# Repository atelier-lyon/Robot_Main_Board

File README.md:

# Robot Main Board
## By Florian "FloRide" Reimat

## About
This is the main board

## Images:
### [Schematic](Export/schematics.pdf):

### [PCB](Export/schematics.pdf):
| Front | Bottom |
:------:|:-------:
|| |
### 3D:
| Front | Bottom |
:------:|:-------:
|| |

## Others:
- [Interactive BOM](Export/ibom/Robot-ibom.html) (Download it and use it)

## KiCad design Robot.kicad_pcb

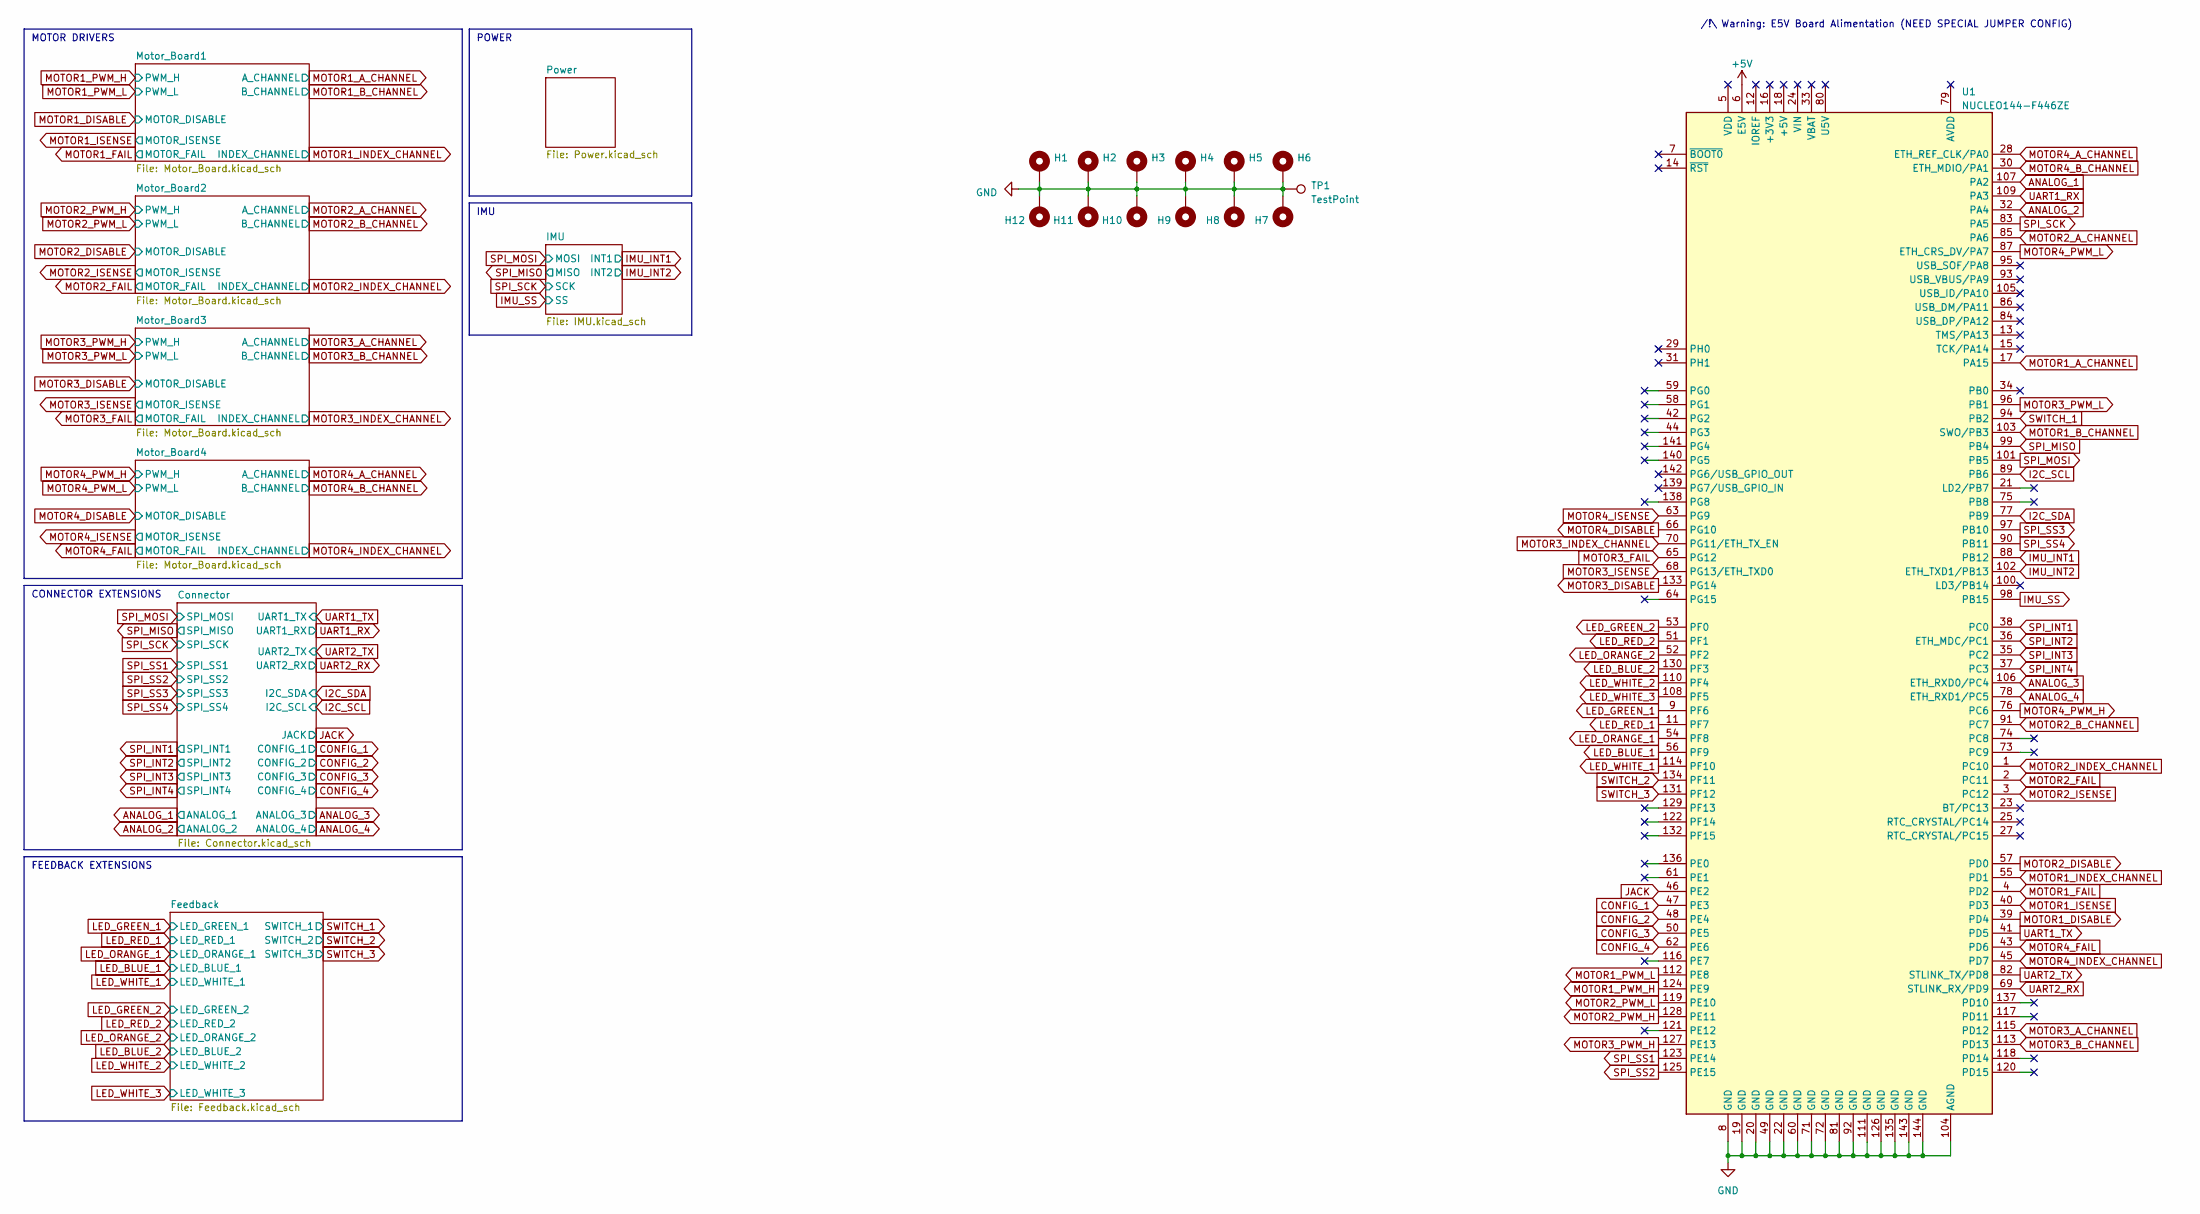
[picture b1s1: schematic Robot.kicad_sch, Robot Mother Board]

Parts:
H1, H2, H3, H4: MountingHole_Pad; MountingHole_4.3mm_M4_Pad
H5, H6, H7, H8, H9, H10, H11, H12: MountingHole_Pad; MountingHole_2.2mm_M2_Pad
TP1: TestPoint; Pin_Croco
U1: NUCLEO144-F446ZE; ST_Morpho_Connector_144_STLink

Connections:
+5V: U1.6 (E5V); also elsewhere on the board
ANALOG_1: U1.107 (PA2); also elsewhere on the board
ANALOG_2: U1.32 (PA4); also elsewhere on the board
ANALOG_3: U1.106 (ETH_RXD0/PC4); also elsewhere on the board
ANALOG_4: U1.78 (ETH_RXD1/PC5); also elsewhere on the board
CONFIG_1: U1.47 (PE3); also elsewhere on the board
CONFIG_2: U1.48 (PE4); also elsewhere on the board
CONFIG_3: U1.50 (PE5); also elsewhere on the board
CONFIG_4: U1.62 (PE6); also elsewhere on the board
GND: H1.1, H2.1, H3.1, H4.1, H5.1, H6.1, H7.1, H8.1, H9.1, H10.1, H11.1, H12.1, TP1.1, U1.8 (GND), U1.19 (GND), U1.20 (GND), U1.22 (GND), U1.49 (GND), U1.60 (GND), U1.71 (GND), U1.72 (GND), U1.81 (GND), U1.92 (GND), U1.104 (AGND), U1.111 (GND), U1.126 (GND), U1.135 (GND), U1.143 (GND), U1.144 (GND); also elsewhere on the board
I2C_SCL: U1.89 (PB6); also elsewhere on the board
I2C_SDA: U1.77 (PB9); also elsewhere on the board
IMU_INT1: U1.88 (PB12); also elsewhere on the board
IMU_INT2: U1.102 (ETH_TXD1/PB13); also elsewhere on the board
IMU_SS: U1.98 (PB15); also elsewhere on the board
JACK: U1.46 (PE2); also elsewhere on the board
LED_BLUE_1: U1.56 (PF9); also elsewhere on the board
LED_BLUE_2: U1.130 (PF3); also elsewhere on the board
LED_GREEN_1: U1.9 (PF6); also elsewhere on the board
LED_GREEN_2: U1.53 (PF0); also elsewhere on the board
LED_ORANGE_1: U1.54 (PF8); also elsewhere on the board
LED_ORANGE_2: U1.52 (PF2); also elsewhere on the board
LED_RED_1: U1.11 (PF7); also elsewhere on the board
LED_RED_2: U1.51 (PF1); also elsewhere on the board
LED_WHITE_1: U1.114 (PF10); also elsewhere on the board
LED_WHITE_2: U1.110 (PF4); also elsewhere on the board
LED_WHITE_3: U1.108 (PF5); also elsewhere on the board
MOTOR1_A_CHANNEL: U1.17 (PA15); also elsewhere on the board
MOTOR1_B_CHANNEL: U1.103 (SWO/PB3); also elsewhere on the board
MOTOR1_DISABLE: U1.39 (PD4); also elsewhere on the board
MOTOR1_FAIL: U1.4 (PD2); also elsewhere on the board
MOTOR1_INDEX_CHANNEL: U1.55 (PD1); also elsewhere on the board
MOTOR1_ISENSE: U1.40 (PD3); also elsewhere on the board
MOTOR1_PWM_H: U1.124 (PE9); also elsewhere on the board
MOTOR1_PWM_L: U1.112 (PE8); also elsewhere on the board
MOTOR2_A_CHANNEL: U1.85 (PA6); also elsewhere on the board
MOTOR2_B_CHANNEL: U1.91 (PC7); also elsewhere on the board
MOTOR2_DISABLE: U1.57 (PD0); also elsewhere on the board
MOTOR2_FAIL: U1.2 (PC11); also elsewhere on the board
MOTOR2_INDEX_CHANNEL: U1.1 (PC10); also elsewhere on the board
MOTOR2_ISENSE: U1.3 (PC12); also elsewhere on the board
MOTOR2_PWM_H: U1.128 (PE11); also elsewhere on the board
MOTOR2_PWM_L: U1.119 (PE10); also elsewhere on the board
MOTOR3_A_CHANNEL: U1.115 (PD12); also elsewhere on the board
MOTOR3_B_CHANNEL: U1.113 (PD13); also elsewhere on the board
MOTOR3_DISABLE: U1.133 (PG14); also elsewhere on the board
MOTOR3_FAIL: U1.65 (PG12); also elsewhere on the board
MOTOR3_INDEX_CHANNEL: U1.70 (PG11/ETH_TX_EN); also elsewhere on the board
MOTOR3_ISENSE: U1.68 (PG13/ETH_TXD0); also elsewhere on the board
MOTOR3_PWM_H: U1.127 (PE13); also elsewhere on the board
MOTOR3_PWM_L: U1.96 (PB1); also elsewhere on the board
MOTOR4_A_CHANNEL: U1.28 (ETH_REF_CLK/PA0); also elsewhere on the board
MOTOR4_B_CHANNEL: U1.30 (ETH_MDIO/PA1); also elsewhere on the board
MOTOR4_DISABLE: U1.66 (PG10); also elsewhere on the board
MOTOR4_FAIL: U1.43 (PD6); also elsewhere on the board
MOTOR4_INDEX_CHANNEL: U1.45 (PD7); also elsewhere on the board
MOTOR4_ISENSE: U1.63 (PG9); also elsewhere on the board
MOTOR4_PWM_H: U1.76 (PC6); also elsewhere on the board
MOTOR4_PWM_L: U1.87 (ETH_CRS_DV/PA7); also elsewhere on the board
SPI_INT1: U1.38 (PC0); also elsewhere on the board
SPI_INT2: U1.36 (ETH_MDC/PC1); also elsewhere on the board
SPI_INT3: U1.35 (PC2); also elsewhere on the board
SPI_INT4: U1.37 (PC3); also elsewhere on the board
SPI_MISO: U1.99 (PB4); also elsewhere on the board
SPI_MOSI: U1.101 (PB5); also elsewhere on the board
SPI_SCK: U1.83 (PA5); also elsewhere on the board
SPI_SS1: U1.123 (PE14); also elsewhere on the board
SPI_SS2: U1.125 (PE15); also elsewhere on the board
SPI_SS3: U1.97 (PB10); also elsewhere on the board
SPI_SS4: U1.90 (PB11); also elsewhere on the board
SWITCH_1: U1.94 (PB2); also elsewhere on the board
SWITCH_2: U1.134 (PF11); also elsewhere on the board
SWITCH_3: U1.131 (PF12); also elsewhere on the board
UART1_RX: U1.109 (PA3); also elsewhere on the board
UART1_TX: U1.41 (PD5); also elsewhere on the board
UART2_RX: U1.69 (STLINK_RX/PD9); also elsewhere on the board
UART2_TX: U1.82 (STLINK_TX/PD8); also elsewhere on the board

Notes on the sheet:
IMU
POWER
CONNECTOR EXTENSIONS
/!\ Warning: E5V Board Alimentation (NEED SPECIAL JUMPER CONFIG)
FEEDBACK EXTENSIONS
MOTOR DRIVERS

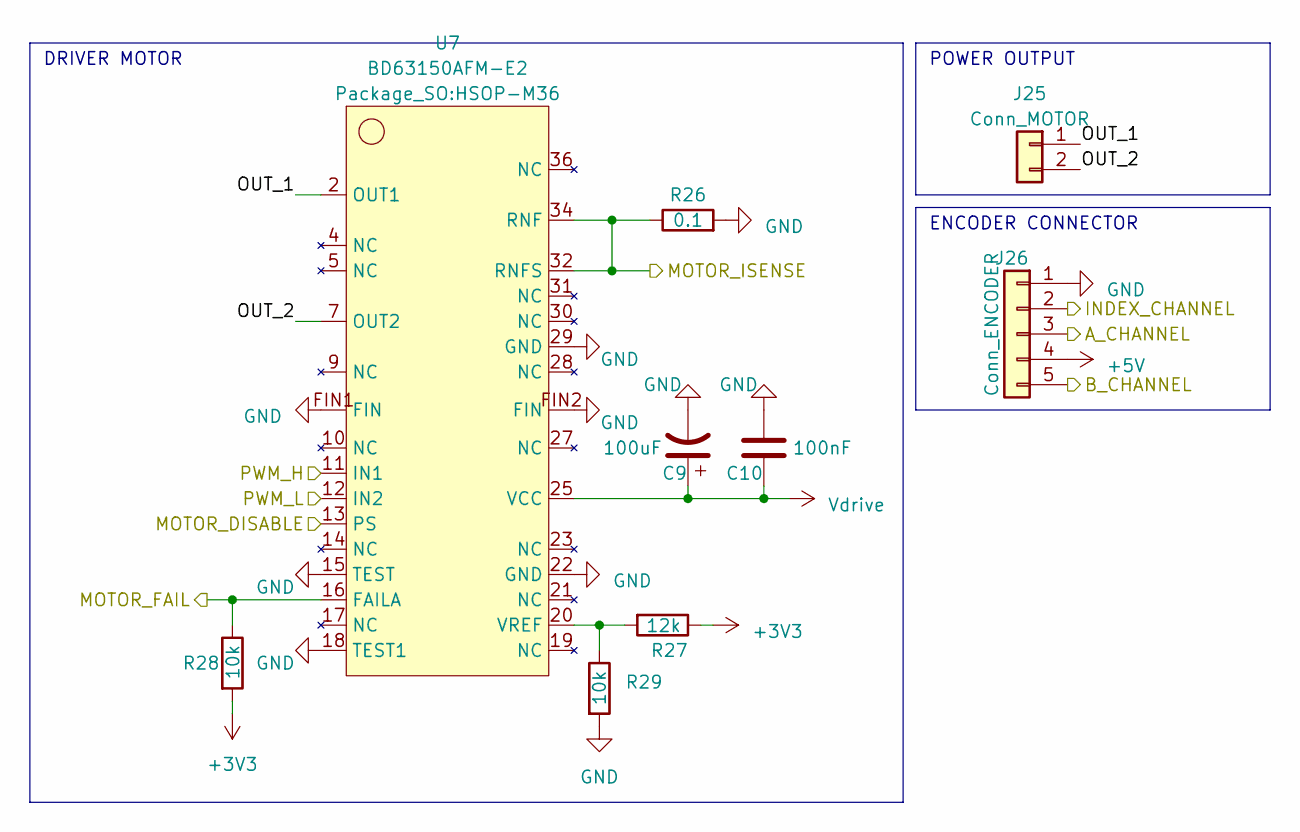
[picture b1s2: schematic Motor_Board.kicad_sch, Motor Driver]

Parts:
C9: 100uF; CP_Radial_D8.0mm_P3.50mm
C10: 100nF; C_0805_2012Metric_Pad1.18x1.45mm_HandSolder
J25: Conn_MOTOR; JST_VH_B2P-VH-B_1x02_P3.96mm_Vertical
J26: Conn_ENCODER; JST_XH_B5B-XH-A_1x05_P2.50mm_Vertical
R26: 0.1; R_2512_6332Metric_Pad1.40x3.35mm_HandSolder
R27: 12k; R_0805_2012Metric_Pad1.20x1.40mm_HandSolder
R28, R29: 10k; R_0805_2012Metric_Pad1.20x1.40mm_HandSolder
U7: BD63150AFM-E2; HSOP-M36

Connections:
+3V3: R27.1, R28.2; also elsewhere on the board
+5V: J26.4; also elsewhere on the board
/Motor_Board1/OUT_1: J25.1, U7.2 (OUT1)
/Motor_Board1/OUT_2: J25.2, U7.7 (OUT2)
GND: C9.2, C10.2, J26.1, R26.2, R29.2, U7.15 (TEST), U7.18 (TEST1), U7.22 (GND), U7.29 (GND), U7.FIN1 (FIN), U7.FIN2 (FIN); also elsewhere on the board
MOTOR1_A_CHANNEL: J26.3; also elsewhere on the board
MOTOR1_B_CHANNEL: J26.5; also elsewhere on the board
MOTOR1_DISABLE: U7.13 (PS); also elsewhere on the board
MOTOR1_FAIL: R28.1, U7.16 (FAILA); also elsewhere on the board
MOTOR1_INDEX_CHANNEL: J26.2; also elsewhere on the board
MOTOR1_ISENSE: R26.1, U7.32 (RNFS), U7.34 (RNF); also elsewhere on the board
MOTOR1_PWM_H: U7.11 (IN1); also elsewhere on the board
MOTOR1_PWM_L: U7.12 (IN2); also elsewhere on the board
unnamed: R27.2, R29.1, U7.20 (VREF)
Vdrive: C9.1, C10.1, U7.25 (VCC); also elsewhere on the board

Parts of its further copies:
C11, C13, C15: 100uF; CP_Radial_D8.0mm_P3.50mm
C12, C14, C16: 100nF; C_0805_2012Metric_Pad1.18x1.45mm_HandSolder
J27, J29, J31: Conn_MOTOR; JST_VH_B2P-VH-B_1x02_P3.96mm_Vertical
J28, J30, J32: Conn_ENCODER; JST_XH_B5B-XH-A_1x05_P2.50mm_Vertical
R30, R34, R38: 0.1; R_2512_6332Metric_Pad1.40x3.35mm_HandSolder
R31, R35, R39: 12k; R_0805_2012Metric_Pad1.20x1.40mm_HandSolder
R32, R33, R36, R37, R40, R41: 10k; R_0805_2012Metric_Pad1.20x1.40mm_HandSolder
U8, U9, U10: BD63150AFM-E2; HSOP-M36

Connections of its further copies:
+3V3: R31.1, R32.2, R35.1, R36.2, R39.1, R40.2; also elsewhere on the board
+5V: J28.4, J30.4, J32.4; also elsewhere on the board
/Motor_Board2/OUT_1: J27.1, U8.2 (OUT1)
/Motor_Board2/OUT_2: J27.2, U8.7 (OUT2)
/Motor_Board3/OUT_1: J29.1, U9.2 (OUT1)
/Motor_Board3/OUT_2: J29.2, U9.7 (OUT2)
/Motor_Board4/OUT_1: J31.1, U10.2 (OUT1)
/Motor_Board4/OUT_2: J31.2, U10.7 (OUT2)
GND: C11.2, C12.2, C13.2, C14.2, C15.2, C16.2, J28.1, J30.1, J32.1, R30.2, R33.2, R34.2, R37.2, R38.2, R41.2, U8.15 (TEST), U8.18 (TEST1), U8.22 (GND), U8.29 (GND), U8.FIN1 (FIN), U8.FIN2 (FIN), U9.15 (TEST), U9.18 (TEST1), U9.22 (GND), U9.29 (GND), U9.FIN1 (FIN), U9.FIN2 (FIN), U10.15 (TEST), U10.18 (TEST1), U10.22 (GND), U10.29 (GND), U10.FIN1 (FIN), U10.FIN2 (FIN); also elsewhere on the board
MOTOR2_A_CHANNEL: J28.3; also elsewhere on the board
MOTOR2_B_CHANNEL: J28.5; also elsewhere on the board
MOTOR2_DISABLE: U8.13 (PS); also elsewhere on the board
MOTOR2_FAIL: R32.1, U8.16 (FAILA); also elsewhere on the board
MOTOR2_INDEX_CHANNEL: J28.2; also elsewhere on the board
MOTOR2_ISENSE: R30.1, U8.32 (RNFS), U8.34 (RNF); also elsewhere on the board
MOTOR2_PWM_H: U8.11 (IN1); also elsewhere on the board
MOTOR2_PWM_L: U8.12 (IN2); also elsewhere on the board
MOTOR3_A_CHANNEL: J30.3; also elsewhere on the board
MOTOR3_B_CHANNEL: J30.5; also elsewhere on the board
MOTOR3_DISABLE: U9.13 (PS); also elsewhere on the board
MOTOR3_FAIL: R36.1, U9.16 (FAILA); also elsewhere on the board
MOTOR3_INDEX_CHANNEL: J30.2; also elsewhere on the board
MOTOR3_ISENSE: R34.1, U9.32 (RNFS), U9.34 (RNF); also elsewhere on the board
MOTOR3_PWM_H: U9.11 (IN1); also elsewhere on the board
MOTOR3_PWM_L: U9.12 (IN2); also elsewhere on the board
MOTOR4_A_CHANNEL: J32.3; also elsewhere on the board
MOTOR4_B_CHANNEL: J32.5; also elsewhere on the board
MOTOR4_DISABLE: U10.13 (PS); also elsewhere on the board
MOTOR4_FAIL: R40.1, U10.16 (FAILA); also elsewhere on the board
MOTOR4_INDEX_CHANNEL: J32.2; also elsewhere on the board
MOTOR4_ISENSE: R38.1, U10.32 (RNFS), U10.34 (RNF); also elsewhere on the board
MOTOR4_PWM_H: U10.11 (IN1); also elsewhere on the board
MOTOR4_PWM_L: U10.12 (IN2); also elsewhere on the board
unnamed: R31.2, R33.1, U8.20 (VREF)
unnamed: R35.2, R37.1, U9.20 (VREF)
unnamed: R39.2, R41.1, U10.20 (VREF)
Vdrive: C11.1, C12.1, C13.1, C14.1, C15.1, C16.1, U8.25 (VCC), U9.25 (VCC), U10.25 (VCC); also elsewhere on the board

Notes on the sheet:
ENCODER CONNECTOR
POWER OUTPUT
DRIVER MOTOR

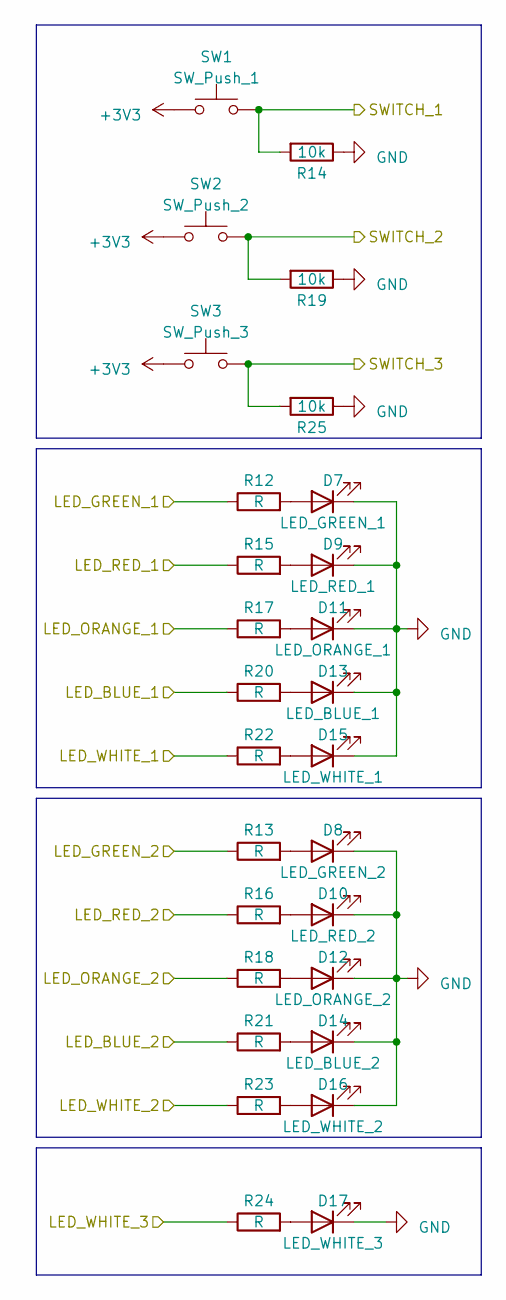
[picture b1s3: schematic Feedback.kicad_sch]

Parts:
D7: LED_GREEN_1; LED_0805_2012Metric_Pad1.15x1.40mm_HandSolder
D8: LED_GREEN_2; LED_0805_2012Metric_Pad1.15x1.40mm_HandSolder
D9: LED_RED_1; LED_0805_2012Metric_Pad1.15x1.40mm_HandSolder
D10: LED_RED_2; LED_0805_2012Metric_Pad1.15x1.40mm_HandSolder
D11: LED_ORANGE_1; LED_0805_2012Metric_Pad1.15x1.40mm_HandSolder
D12: LED_ORANGE_2; LED_0805_2012Metric_Pad1.15x1.40mm_HandSolder
D13: LED_BLUE_1; LED_0805_2012Metric_Pad1.15x1.40mm_HandSolder
D14: LED_BLUE_2; LED_0805_2012Metric_Pad1.15x1.40mm_HandSolder
D15: LED_WHITE_1; LED_0805_2012Metric_Pad1.15x1.40mm_HandSolder
D16: LED_WHITE_2; LED_0805_2012Metric_Pad1.15x1.40mm_HandSolder
D17: LED_WHITE_3; LED_0805_2012Metric_Pad1.15x1.40mm_HandSolder
R12, R13, R15, R16, R17, R18, R20, R21, R22, R23, R24: R; R_0805_2012Metric_Pad1.20x1.40mm_HandSolder
R14, R19, R25: 10k; R_0805_2012Metric_Pad1.20x1.40mm_HandSolder
SW1: SW_Push_1; SW_Tactile_Straight_KSL0Axx1LFTR
SW2: SW_Push_2; SW_Tactile_Straight_KSL0Axx1LFTR
SW3: SW_Push_3; SW_Tactile_Straight_KSL0Axx1LFTR

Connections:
+3V3: SW1.1, SW2.1, SW3.1; also elsewhere on the board
GND: D7.1 (K), D8.1 (K), D9.1 (K), D10.1 (K), D11.1 (K), D12.1 (K), D13.1 (K), D14.1 (K), D15.1 (K), D16.1 (K), D17.1 (K), R14.1, R19.1, R25.1; also elsewhere on the board
LED_BLUE_1: R20.1; also elsewhere on the board
LED_BLUE_2: R21.1; also elsewhere on the board
LED_GREEN_1: R12.1; also elsewhere on the board
LED_GREEN_2: R13.1; also elsewhere on the board
LED_ORANGE_1: R17.1; also elsewhere on the board
LED_ORANGE_2: R18.1; also elsewhere on the board
LED_RED_1: R15.1; also elsewhere on the board
LED_RED_2: R16.1; also elsewhere on the board
LED_WHITE_1: R22.1; also elsewhere on the board
LED_WHITE_2: R23.1; also elsewhere on the board
LED_WHITE_3: R24.1; also elsewhere on the board
unnamed: D7.2 (A), R12.2
unnamed: D8.2 (A), R13.2
unnamed: D9.2 (A), R15.2
unnamed: D10.2 (A), R16.2
unnamed: D11.2 (A), R17.2
unnamed: D12.2 (A), R18.2
unnamed: D13.2 (A), R20.2
unnamed: D14.2 (A), R21.2
unnamed: D15.2 (A), R22.2
unnamed: D16.2 (A), R23.2
unnamed: D17.2 (A), R24.2
SWITCH_1: R14.2, SW1.2; also elsewhere on the board
SWITCH_2: R19.2, SW2.2; also elsewhere on the board
SWITCH_3: R25.2, SW3.2; also elsewhere on the board

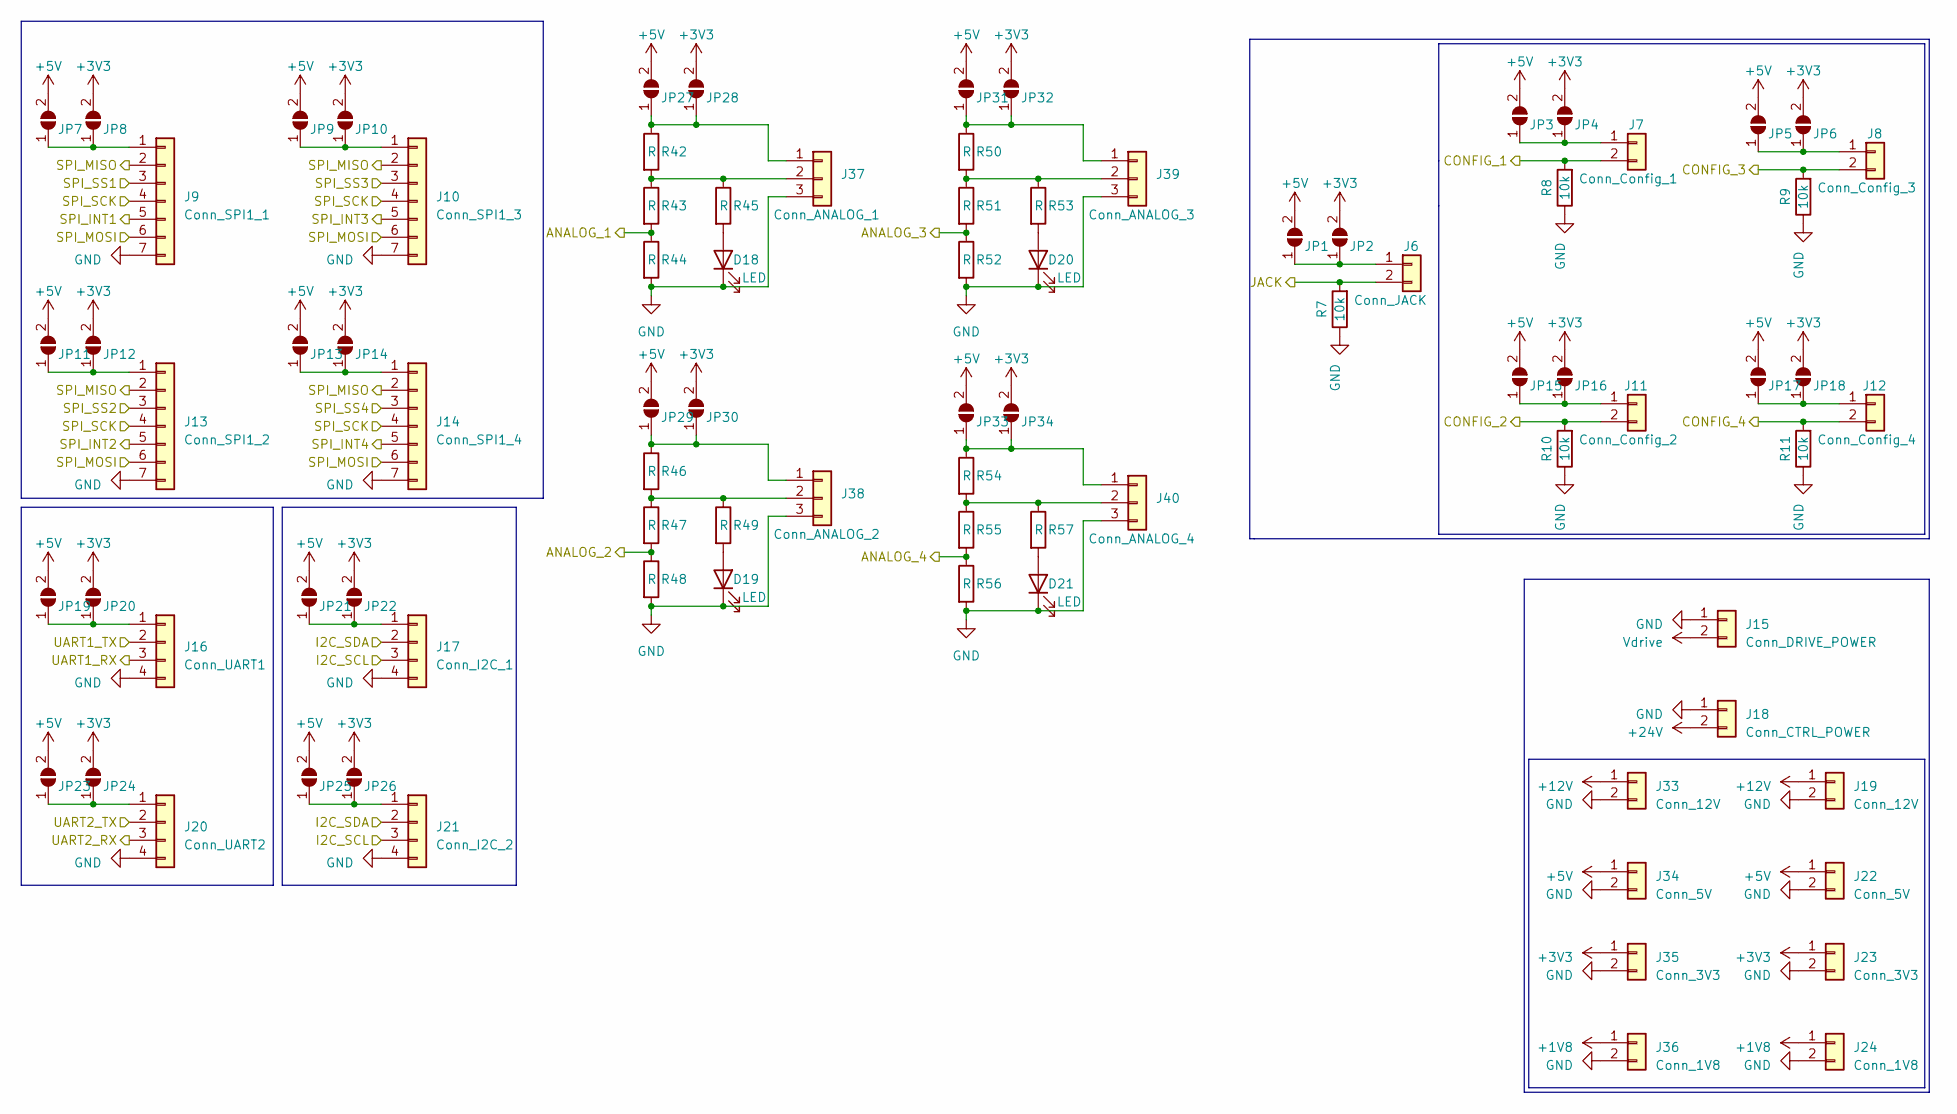
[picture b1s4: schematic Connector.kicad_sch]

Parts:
D18, D19, D20, D21: LED; LED_0805_2012Metric_Pad1.15x1.40mm_HandSolder
J6: Conn_JACK; JST_XH_B2B-XH-A_1x02_P2.50mm_Vertical
J7: Conn_Config_1; JST_XH_B2B-XH-A_1x02_P2.50mm_Vertical
J8: Conn_Config_3; JST_XH_B2B-XH-A_1x02_P2.50mm_Vertical
J9: Conn_SPI1_1; JST_XH_B7B-XH-A_1x07_P2.50mm_Vertical
J10: Conn_SPI1_3; JST_XH_B7B-XH-A_1x07_P2.50mm_Vertical
J11: Conn_Config_2; JST_XH_B2B-XH-A_1x02_P2.50mm_Vertical
J12: Conn_Config_4; JST_XH_B2B-XH-A_1x02_P2.50mm_Vertical
J13: Conn_SPI1_2; JST_XH_B7B-XH-A_1x07_P2.50mm_Vertical
J14: Conn_SPI1_4; JST_XH_B7B-XH-A_1x07_P2.50mm_Vertical
J15: Conn_DRIVE_POWER; AMASS_XT60-F_1x02_P7.20mm_Vertical
J16: Conn_UART1; JST_XH_B4B-XH-A_1x04_P2.50mm_Vertical
J17: Conn_I2C_1; JST_XH_B4B-XH-A_1x04_P2.50mm_Vertical
J18: Conn_CTRL_POWER; AMASS_XT60-F_1x02_P7.20mm_Vertical
J19, J33: Conn_12V; JST_XH_B2B-XH-A_1x02_P2.50mm_Vertical
J20: Conn_UART2; JST_XH_B4B-XH-A_1x04_P2.50mm_Vertical
J21: Conn_I2C_2; JST_XH_B4B-XH-A_1x04_P2.50mm_Vertical
J22, J34: Conn_5V; JST_XH_B2B-XH-A_1x02_P2.50mm_Vertical
J23, J35: Conn_3V3; JST_XH_B2B-XH-A_1x02_P2.50mm_Vertical
J24, J36: Conn_1V8; JST_XH_B2B-XH-A_1x02_P2.50mm_Vertical
J37: Conn_ANALOG_1; JST_XH_B3B-XH-A_1x03_P2.50mm_Vertical
J38: Conn_ANALOG_2; JST_XH_B3B-XH-A_1x03_P2.50mm_Vertical
J39: Conn_ANALOG_3; JST_XH_B3B-XH-A_1x03_P2.50mm_Vertical
J40: Conn_ANALOG_4; JST_XH_B3B-XH-A_1x03_P2.50mm_Vertical
JP1, JP2, JP3, JP4, JP5, JP6, JP7, JP8, JP9, JP10, JP11, JP12, JP13, JP14, JP15, JP16, JP17, JP18, JP19, JP20, JP21, JP22, JP23, JP24, JP25, JP26, JP27, JP28, JP29, JP30, JP31, JP32, JP33, JP34: SolderJumper_2_Open; SolderJumper-2_P1.3mm_Open_TrianglePad1.0x1.5mm
R7, R8, R9, R10, R11: 10k; R_0805_2012Metric_Pad1.20x1.40mm_HandSolder
R42, R43, R44, R45, R46, R47, R48, R49, R50, R51, R52, R53, R54, R55, R56, R57: R; R_0805_2012Metric_Pad1.20x1.40mm_HandSolder

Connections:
+1V8: J24.1, J36.1; also elsewhere on the board
+3V3: J23.1, J35.1, JP2.2 (B), JP4.2 (B), JP6.2 (B), JP8.2 (B), JP10.2 (B), JP12.2 (B), JP14.2 (B), JP16.2 (B), JP18.2 (B), JP20.2 (B), JP22.2 (B), JP24.2 (B), JP26.2 (B), JP28.2 (B), JP30.2 (B), JP32.2 (B), JP34.2 (B); also elsewhere on the board
+5V: J22.1, J34.1, JP1.2 (B), JP3.2 (B), JP5.2 (B), JP7.2 (B), JP9.2 (B), JP11.2 (B), JP13.2 (B), JP15.2 (B), JP17.2 (B), JP19.2 (B), JP21.2 (B), JP23.2 (B), JP25.2 (B), JP27.2 (B), JP29.2 (B), JP31.2 (B), JP33.2 (B); also elsewhere on the board
+12V: J19.1, J33.1; also elsewhere on the board
+24V: J18.2; also elsewhere on the board
ANALOG_1: R43.2, R44.1; also elsewhere on the board
ANALOG_2: R47.2, R48.1; also elsewhere on the board
ANALOG_3: R51.2, R52.1; also elsewhere on the board
ANALOG_4: R55.2, R56.1; also elsewhere on the board
CONFIG_1: J7.2, R8.2; also elsewhere on the board
CONFIG_2: J11.2, R10.2; also elsewhere on the board
CONFIG_3: J8.2, R9.2; also elsewhere on the board
CONFIG_4: J12.2, R11.2; also elsewhere on the board
GND: D18.1 (K), D19.1 (K), D20.1 (K), D21.1 (K), J9.7, J10.7, J13.7, J14.7, J15.1, J16.4, J17.4, J18.1, J19.2, J20.4, J21.4, J22.2, J23.2, J24.2, J33.2, J34.2, J35.2, J36.2, J37.3, J38.3, J39.3, J40.3, R7.1, R8.1, R9.1, R10.1, R11.1, R44.2, R48.2, R52.2, R56.2; also elsewhere on the board
I2C_SCL: J17.3, J21.3; also elsewhere on the board
I2C_SDA: J17.2, J21.2; also elsewhere on the board
JACK: J6.2, R7.2; also elsewhere on the board
unnamed: D18.2 (A), R45.2
unnamed: D19.2 (A), R49.2
unnamed: D20.2 (A), R53.2
unnamed: D21.2 (A), R57.2
unnamed: J6.1, JP1.1 (A), JP2.1 (A)
unnamed: J7.1, JP3.1 (A), JP4.1 (A)
unnamed: J8.1, JP5.1 (A), JP6.1 (A)
unnamed: J9.1, JP7.1 (A), JP8.1 (A)
unnamed: J10.1, JP9.1 (A), JP10.1 (A)
unnamed: J11.1, JP15.1 (A), JP16.1 (A)
unnamed: J12.1, JP17.1 (A), JP18.1 (A)
unnamed: J13.1, JP11.1 (A), JP12.1 (A)
unnamed: J14.1, JP13.1 (A), JP14.1 (A)
unnamed: J16.1, JP19.1 (A), JP20.1 (A)
unnamed: J17.1, JP21.1 (A), JP22.1 (A)
unnamed: J20.1, JP23.1 (A), JP24.1 (A)
unnamed: J21.1, JP25.1 (A), JP26.1 (A)
unnamed: J37.1, JP27.1 (A), JP28.1 (A), R42.1
unnamed: J37.2, R42.2, R43.1, R45.1
unnamed: J38.1, JP29.1 (A), JP30.1 (A), R46.1
unnamed: J38.2, R46.2, R47.1, R49.1
unnamed: J39.1, JP31.1 (A), JP32.1 (A), R50.1
unnamed: J39.2, R50.2, R51.1, R53.1
unnamed: J40.1, JP33.1 (A), JP34.1 (A), R54.1
unnamed: J40.2, R54.2, R55.1, R57.1
SPI_INT1: J9.5; also elsewhere on the board
SPI_INT2: J13.5; also elsewhere on the board
SPI_INT3: J10.5; also elsewhere on the board
SPI_INT4: J14.5; also elsewhere on the board
SPI_MISO: J9.2, J10.2, J13.2, J14.2; also elsewhere on the board
SPI_MOSI: J9.6, J10.6, J13.6, J14.6; also elsewhere on the board
SPI_SCK: J9.4, J10.4, J13.4, J14.4; also elsewhere on the board
SPI_SS1: J9.3; also elsewhere on the board
SPI_SS2: J13.3; also elsewhere on the board
SPI_SS3: J10.3; also elsewhere on the board
SPI_SS4: J14.3; also elsewhere on the board
UART1_RX: J16.3; also elsewhere on the board
UART1_TX: J16.2; also elsewhere on the board
UART2_RX: J20.3; also elsewhere on the board
UART2_TX: J20.2; also elsewhere on the board
Vdrive: J15.2; also elsewhere on the board

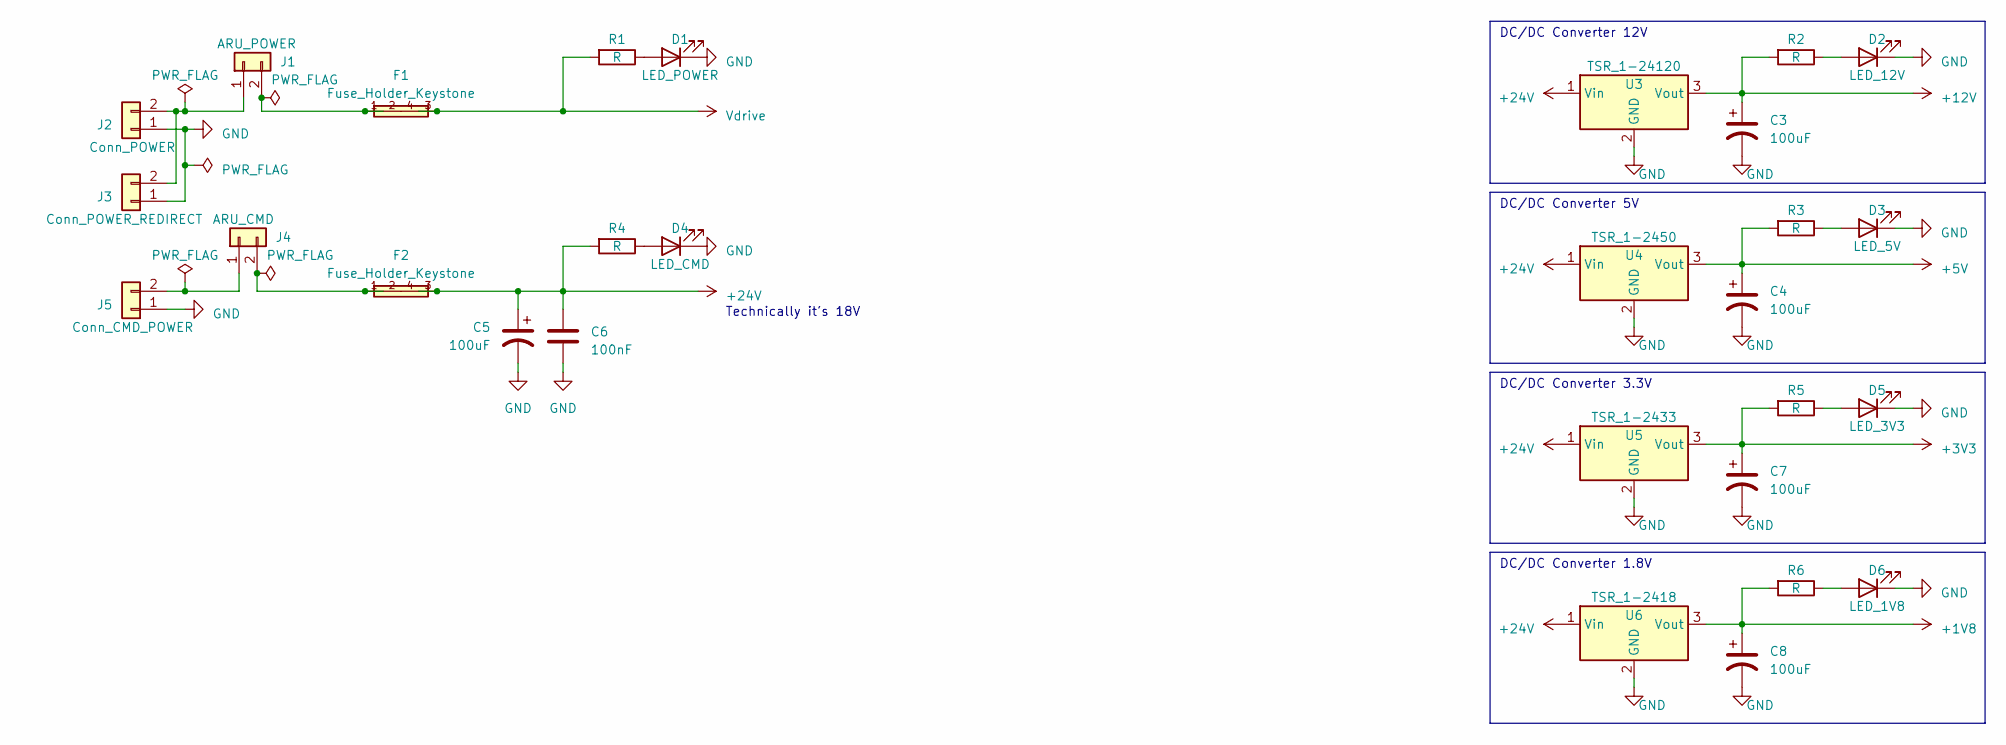
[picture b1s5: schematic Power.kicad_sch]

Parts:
C3, C4, C5, C7, C8: 100uF; CP_Radial_D8.0mm_P3.50mm
C6: 100nF; C_0805_2012Metric_Pad1.18x1.45mm_HandSolder
D1: LED_POWER; LED_0805_2012Metric_Pad1.15x1.40mm_HandSolder
D2: LED_12V; LED_0805_2012Metric_Pad1.15x1.40mm_HandSolder
D3: LED_5V; LED_0805_2012Metric_Pad1.15x1.40mm_HandSolder
D4: LED_CMD; LED_0805_2012Metric_Pad1.15x1.40mm_HandSolder
D5: LED_3V3; LED_0805_2012Metric_Pad1.15x1.40mm_HandSolder
D6: LED_1V8; LED_0805_2012Metric_Pad1.15x1.40mm_HandSolder
F1, F2: Fuse_Holder_Keystone; Fuseholder_Keystone_3557-2
J1: ARU_POWER; AMASS_XT60-F_1x02_P7.20mm_Vertical
J2: Conn_POWER; AMASS_XT60-M_1x02_P7.20mm_Vertical
J3: Conn_POWER_REDIRECT; AMASS_XT60-F_1x02_P7.20mm_Vertical
J4: ARU_CMD; AMASS_XT60-F_1x02_P7.20mm_Vertical
J5: Conn_CMD_POWER; AMASS_XT60-M_1x02_P7.20mm_Vertical
R1, R2, R3, R4, R5, R6: R; R_0805_2012Metric_Pad1.20x1.40mm_HandSolder
U3: TSR_1-24120; Converter_DCDC_TRACO_TSR-1_THT
U4: TSR_1-2450; Converter_DCDC_TRACO_TSR-1_THT
U5: TSR_1-2433; Converter_DCDC_TRACO_TSR-1_THT
U6: TSR_1-2418; Converter_DCDC_TRACO_TSR-1_THT

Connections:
+1V8: C8.1, R6.2, U6.3 (Vout); also elsewhere on the board
+3V3: C7.1, R5.2, U5.3 (Vout); also elsewhere on the board
+5V: C4.1, R3.2, U4.3 (Vout); also elsewhere on the board
+12V: C3.1, R2.2, U3.3 (Vout); also elsewhere on the board
+24V: C5.1, C6.1, F2.3, F2.4, R4.2, U3.1 (Vin), U4.1 (Vin), U5.1 (Vin), U6.1 (Vin); also elsewhere on the board
GND: C3.2, C4.2, C5.2, C6.2, C7.2, C8.2, D1.1 (K), D2.1 (K), D3.1 (K), D4.1 (K), D5.1 (K), D6.1 (K), J2.1, J3.1, J5.1, U3.2 (GND), U4.2 (GND), U5.2 (GND), U6.2 (GND); also elsewhere on the board
unnamed: D1.2 (A), R1.1
unnamed: D2.2 (A), R2.1
unnamed: D3.2 (A), R3.1
unnamed: D4.2 (A), R4.1
unnamed: D5.2 (A), R5.1
unnamed: D6.2 (A), R6.1
unnamed: J1.1, J2.2, J3.2
unnamed: F1.1, F1.2, J1.2
unnamed: J4.1, J5.2
unnamed: F2.1, F2.2, J4.2
Vdrive: F1.3, F1.4, R1.2; also elsewhere on the board

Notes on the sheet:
DC/DC Converter 12V
DC/DC Converter 3.3V
DC/DC Converter 5V
DC/DC Converter 1.8V
Technically it's 18V

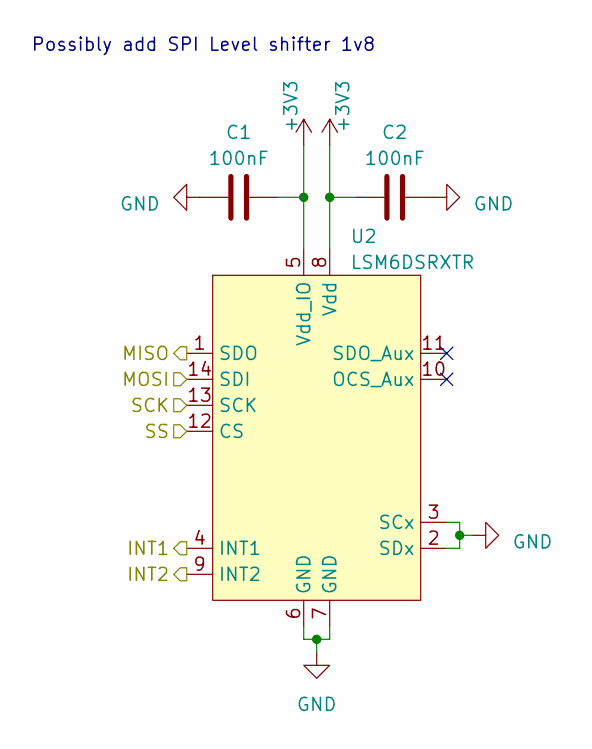
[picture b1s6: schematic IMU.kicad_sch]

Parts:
C1, C2: 100nF; C_0805_2012Metric_Pad1.18x1.45mm_HandSolder
U2: LSM6DSRXTR; LGA-14_3x2.5mm_P0.5mm_LayoutBorder3x4y

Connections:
+3V3: C1.2, C2.1, U2.5 (Vdd_IO), U2.8 (Vdd); also elsewhere on the board
GND: C1.1, C2.2, U2.2 (SDx), U2.3 (SCx), U2.6 (GND), U2.7 (GND); also elsewhere on the board
IMU_INT1: U2.4 (INT1); also elsewhere on the board
IMU_INT2: U2.9 (INT2); also elsewhere on the board
IMU_SS: U2.12 (CS); also elsewhere on the board
SPI_MISO: U2.1 (SDO); also elsewhere on the board
SPI_MOSI: U2.14 (SDI); also elsewhere on the board
SPI_SCK: U2.13 (SCK); also elsewhere on the board

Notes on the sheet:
Possibly add SPI Level shifter 1v8
